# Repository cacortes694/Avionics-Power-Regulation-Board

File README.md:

Power Regulation Board for the Fresno State SLI Full Scale Avionics Bay

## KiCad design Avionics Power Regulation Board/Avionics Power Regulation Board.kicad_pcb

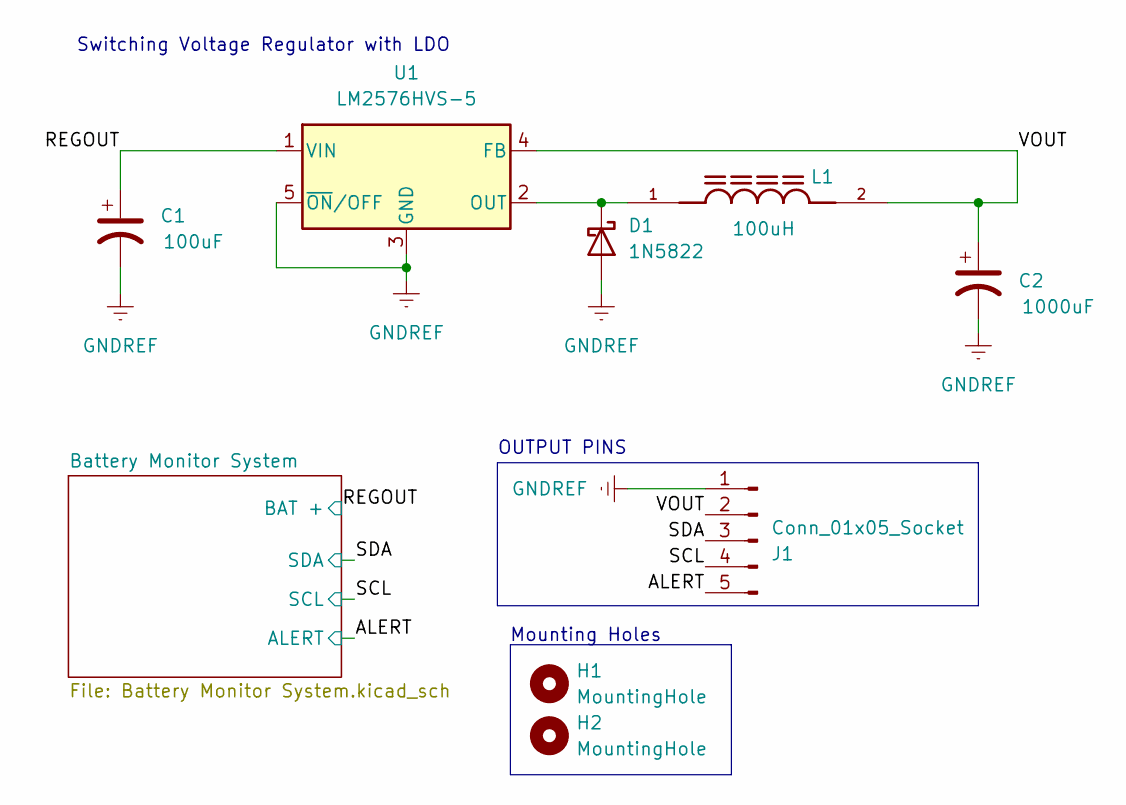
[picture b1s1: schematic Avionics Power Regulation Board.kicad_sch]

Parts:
C1: EEUFR1V101B; C_Radial_D5.0mm_H11.0mm_P2.00mm; PARTREV 28-FEB-20
C2: EEUTA1V102; C_Radial_D10.0mm_H16.0mm_P5.00mm; PARTREV 20-DEC-19
D1: 1N5822; D_DO-201AD_P15.24mm_Horizontal
H1, H2: MountingHole; MountingHole_2.1mm
J1: Conn_01x05_Socket; PinHeader_1x05_P2.54mm_Vertical
L1: RC-10; L_Radial_D6.0mm_P4.00mm; PARTREV 07/21
U1: LM2576HVS-5; TO-263-5_TabPin3

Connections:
/ALERT: J1.5; also elsewhere on the board
/REGOUT: C1.1, U1.1 (VIN); also elsewhere on the board
/SCL: J1.4; also elsewhere on the board
/SDA: J1.3; also elsewhere on the board
/VOUT: C2.1, J1.2, L1.2, U1.4 (FB)
GNDREF: C1.2, C2.2, D1.2 (A), J1.1, U1.3 (GND), U1.5 (~ON/OFF); also elsewhere on the board
unnamed: D1.1 (K), L1.1, U1.2 (OUT)

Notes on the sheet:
OUTPUT PINS
Switching Voltage Regulator with LDO
Mounting Holes

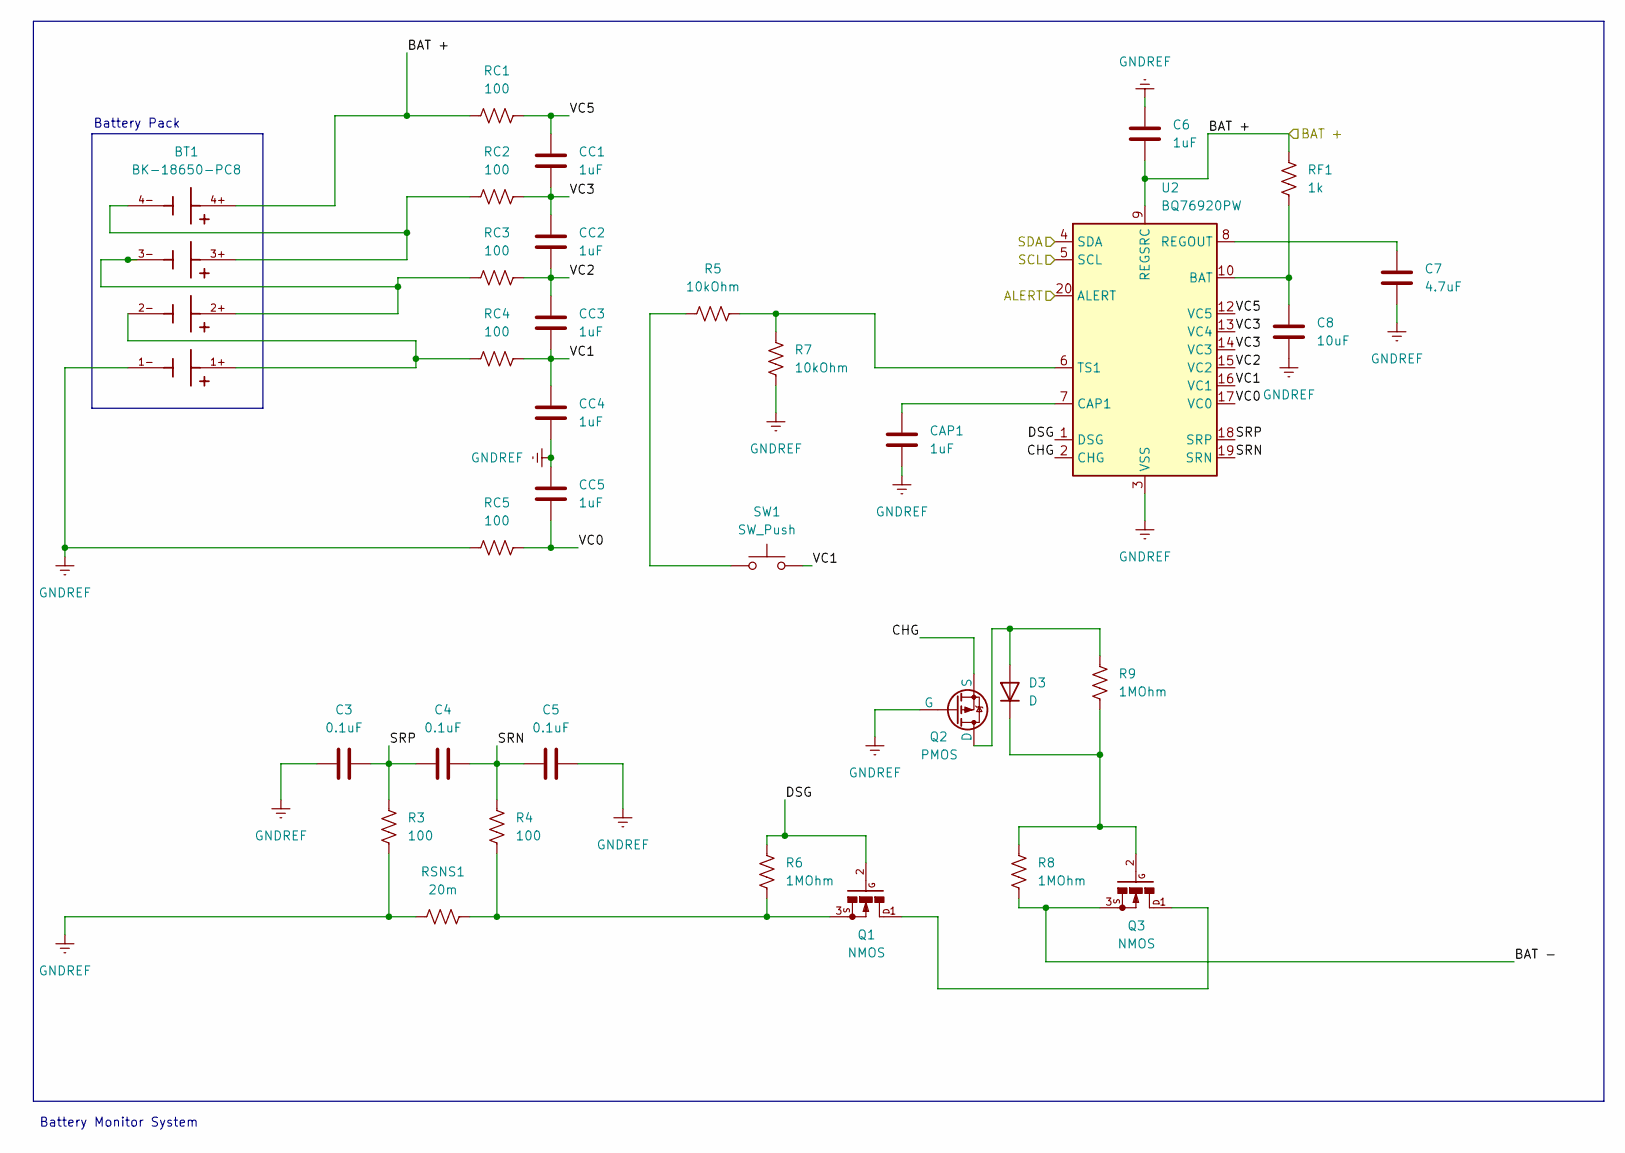
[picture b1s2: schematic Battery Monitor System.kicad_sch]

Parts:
BT1: BK-18650-PC8; BAT_BK-18650-PC8; PARTREV L
C3, C4, C5: 0.1uF; C_Radial_D4.0mm_H7.0mm_P1.50mm
C6: 1uF; C_Radial_D5.0mm_H11.0mm_P2.00mm
C7: 4.7uF; C_Radial_D4.0mm_H7.0mm_P1.50mm
C8: 10uF; C_Radial_D5.0mm_H11.0mm_P2.00mm
CAP1: 1uF; C_Radial_D5.0mm_H11.0mm_P2.00mm
CC1, CC2, CC3, CC4, CC5: 1uF; C_Radial_D5.0mm_H11.0mm_P2.00mm
D3: D; D_DO-41_SOD81_P10.16mm_Horizontal
Q1, Q3: NMOS; TO92
Q2: PMOS; TO92
R3, R4: 100; R_0805_2012Metric_Pad1.20x1.40mm_HandSolder
R5, R7: 10kOhm; R_0805_2012Metric_Pad1.20x1.40mm_HandSolder
R6, R8, R9: 1MOhm; R_0805_2012Metric_Pad1.20x1.40mm_HandSolder
RC1, RC2, RC3, RC4, RC5: 100; R_0805_2012Metric_Pad1.20x1.40mm_HandSolder
RF1: 1k; R_0805_2012Metric_Pad1.20x1.40mm_HandSolder
RSNS1: 20m; R_0805_2012Metric_Pad1.20x1.40mm_HandSolder
SW1: SW_Push; SW_PUSH_6mm
U2: BQ76920PW; TSSOP-20_4.4x6.5mm_P0.65mm

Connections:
/ALERT: U2.20 (ALERT); also elsewhere on the board
/Battery Monitor System/BAT -: Q3.3, R8.1
/Battery Monitor System/CHG: Q2.3 (S), U2.2 (CHG)
/Battery Monitor System/DSG: Q1.2, R6.2, U2.1 (DSG)
/Battery Monitor System/SRN: C4.2, C5.1, R4.1, U2.19 (SRN)
/Battery Monitor System/SRP: C3.2, C4.1, R3.1, U2.18 (SRP)
/Battery Monitor System/VC0: CC5.2, RC5.2, U2.17 (VC0)
/Battery Monitor System/VC1: CC3.2, CC4.1, RC4.2, SW1.2, U2.16 (VC1)
/Battery Monitor System/VC2: CC2.2, CC3.1, RC3.2, U2.15 (VC2)
/Battery Monitor System/VC3: CC1.2, CC2.1, RC2.2, U2.13 (VC4), U2.14 (VC3)
/Battery Monitor System/VC5: CC1.1, RC1.2, U2.12 (VC5)
/REGOUT: BT1.4+, C6.1, RC1.1, RF1.2, U2.9 (REGSRC); also elsewhere on the board
/SCL: U2.5 (SCL); also elsewhere on the board
/SDA: U2.4 (SDA); also elsewhere on the board
GNDREF: BT1.1-, C3.1, C5.2, C6.2, C7.1, C8.1, CAP1.2, CC4.2, CC5.1, Q2.2 (G), R3.2, R7.1, RC5.1, RSNS1.1, U2.3 (VSS); also elsewhere on the board
unnamed: BT1.1+, BT1.2-, RC4.1
unnamed: BT1.2+, BT1.3-, RC3.1
unnamed: BT1.3+, BT1.4-, RC2.1
unnamed: D3.2 (A), Q2.1 (D), R9.2
unnamed: D3.1 (K), Q3.2, R8.2, R9.1
unnamed: Q1.1, Q3.1
unnamed: Q1.3, R4.2, R6.1, RSNS1.2
unnamed: R5.1, SW1.1
unnamed: C8.2, RF1.1, U2.10 (BAT)
unnamed: CAP1.1, U2.7 (CAP1)
unnamed: C7.2, U2.8 (REGOUT)
unnamed: R5.2, R7.2, U2.6 (TS1)

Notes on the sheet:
Battery Monitor System
Battery Pack

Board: 2 copper layers, 41 parts (0 on the bottom side), 29 nets, no tracks yet.

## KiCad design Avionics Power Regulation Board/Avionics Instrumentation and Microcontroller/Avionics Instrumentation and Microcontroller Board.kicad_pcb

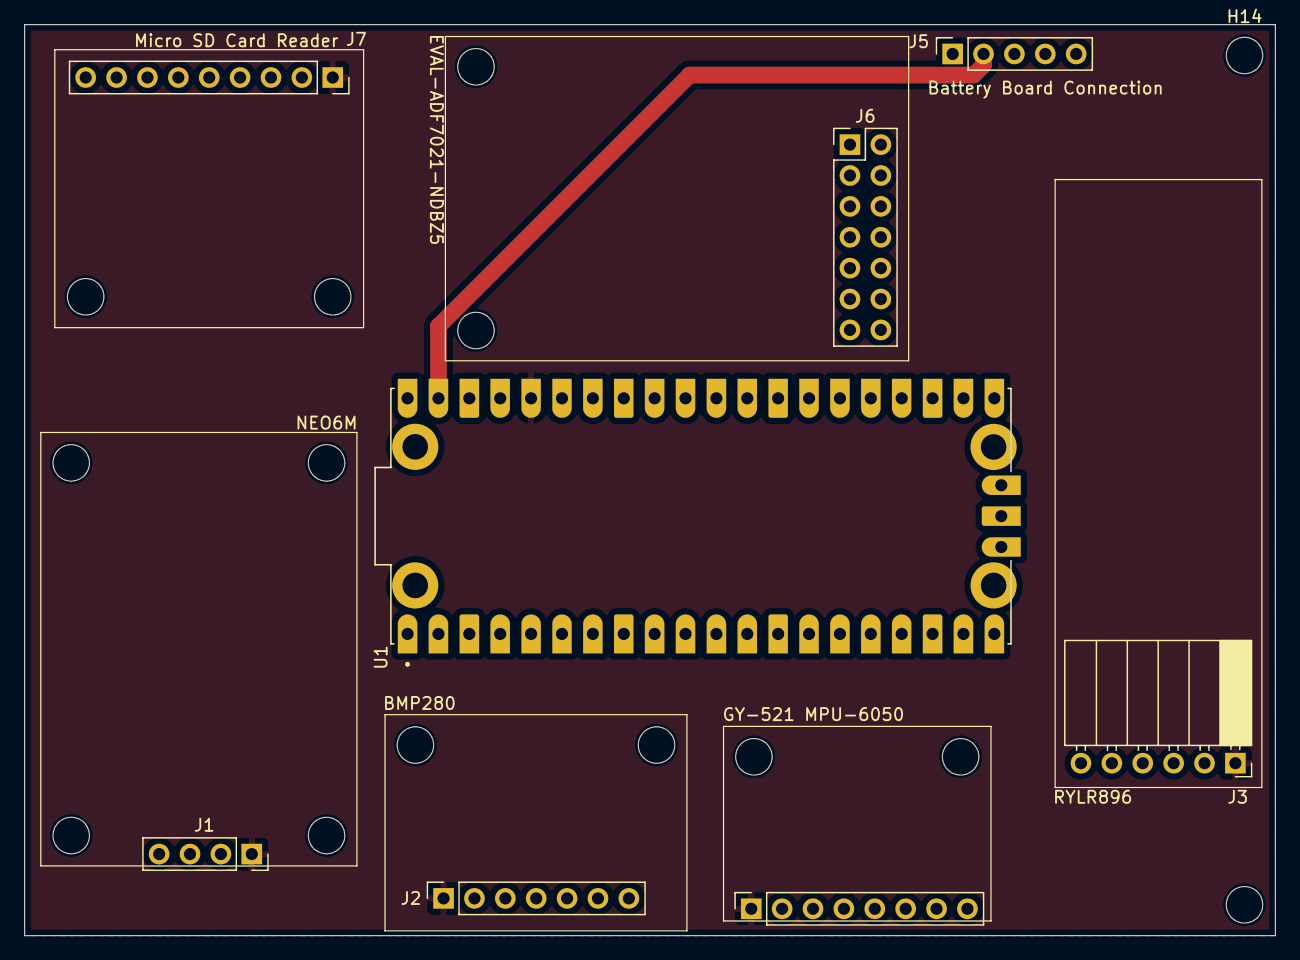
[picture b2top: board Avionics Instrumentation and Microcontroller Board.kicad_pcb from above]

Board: 2 copper layers, 102.9 x 74.9 mm, 22 parts (0 on the bottom side), 3 nets.

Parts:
H1, H2, H3, H4, H5, H6, H7, H8, H9, H10, H11, H12, H13, H14: MountingHole; MountingHole_2.1mm
J1: Conn_01x04_Socket; PinSocket_1x04_P2.54mm_Vertical
J2: Conn_01x07_Socket; PinSocket_1x07_P2.54mm_Vertical
J3: Conn_01x06_Socket; PinSocket_1x06_P2.54mm_Horizontal
J4: Conn_01x08_Socket; PinSocket_1x08_P2.54mm_Vertical
J5: Conn_01x05_Socket; PinSocket_1x05_P2.54mm_Vertical
J6: Conn_02x07_Odd_Even; PinHeader_2x07_P2.54mm_Vertical
J7: Conn_01x09_Socket; PinSocket_1x09_P2.54mm_Vertical
U1: SC0917; MODULE_SC0917

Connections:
/3.3V: J1.1, J2.1, J3.1, J4.1, J7.1, U1.36 (3V3_OUT)
/Vin: J5.2, U1.39 (VSYS)
GNDREF: J1.4, J2.3, J3.6, J4.2, J5.1, J7.2, U1.3 (GND), U1.8 (GND), U1.13 (GND), U1.18 (GND), U1.23 (GND), U1.28 (GND), U1.33 (AGND), U1.38 (GND), U1.D2 (GND)

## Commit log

2024-12-02 Uploading the KiCad Files
2024-12-02 deletions
2024-12-03 Updated Subscale Board
2024-12-03 Updated Subscale Part 2
2024-12-03 Updated Subscale Part 3
2024-12-03 Radio Added
2024-12-03 added radio
2024-12-07 Added Accurate footprints
2024-12-07 Test PCB Layout
2024-12-07 Last Push
2024-12-07 Completely Redone
2024-12-07 Last Minute Changes
2024-12-07 Photos
2024-12-08 Small Edits
2024-12-08 Small PCB Edits
2024-12-10 Miku
2024-12-10 Changed Inductor
2024-12-10 Small Changes
2024-12-11 Small Updates
2024-12-12 Fixed PMOS
2024-12-12 Fixed
2024-12-24 Step Files
2024-12-24 Step
2024-12-24 gerbers
2024-12-24 End of Tonight
2024-12-26 Extra touches
2024-12-29 Adding to the Avionics Sensors Board
2024-12-30 Instrumentation Layout WIP
2024-12-31 more changes
2024-12-31 Checking Gerbers
2025-01-04 Removed one of the transformer
    Must Redo the traces when you get home
